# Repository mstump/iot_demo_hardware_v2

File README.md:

iot_demo_hardware_v2
====================

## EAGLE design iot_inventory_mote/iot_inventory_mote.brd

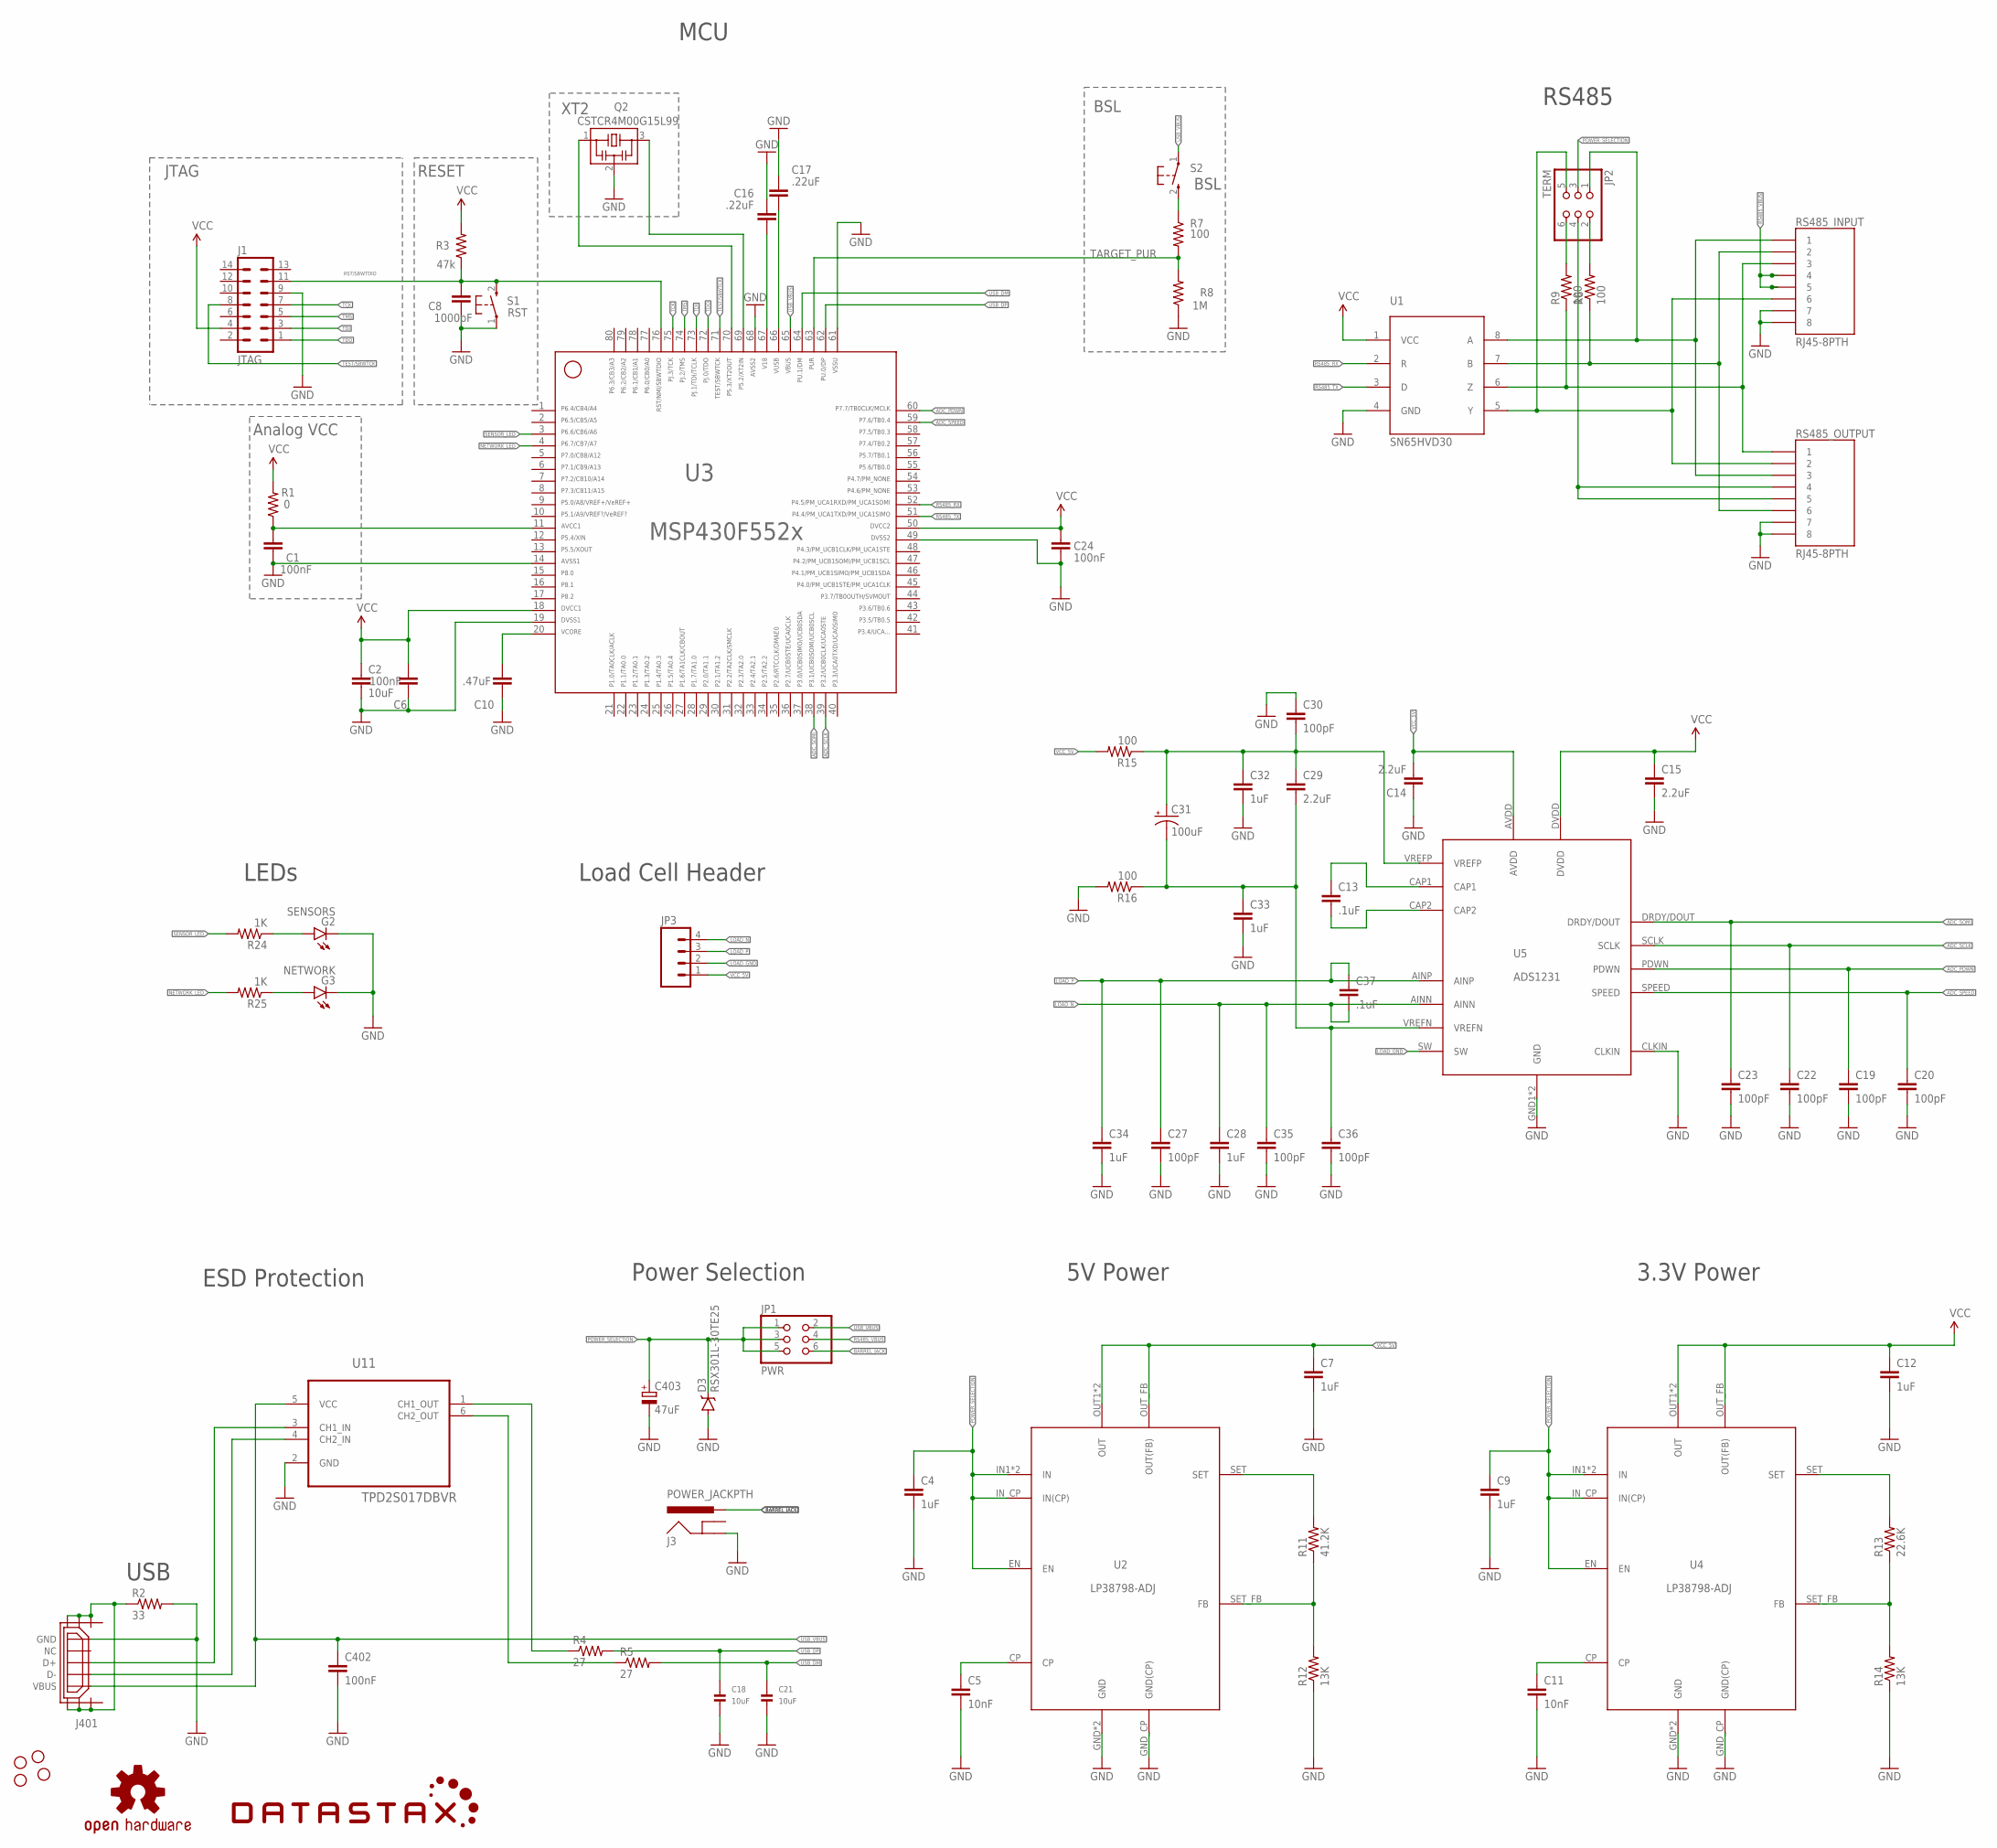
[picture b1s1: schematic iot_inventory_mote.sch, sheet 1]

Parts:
C1, C6, C24: 100nF; 0402-CAP
C2: 10uF; 0402-CAP
C4, C7, C9, C12: 1uF; 0402-CAP
C5, C11: 10nF; 0402-CAP
C8: 1000pF; 0402-CAP; MPN C1005X7R1H102K050BA
C10: .47uF; 0402-CAP
C13, C37: .1uF; 1210
C14, C15, C29: 2.2uF; 0402-CAP
C16, C17: .22uF; 0402-CAP
C18, C21: 10uF; 0603; MPN 06035A100FAT2A
C19, C20, C22, C23: 100pF; 0805
C27, C30, C35, C36: 100pF; 0603-CAP
C28, C32, C33, C34: 1uF; 0805
C31: 100uF; EIA7343
C402: 100nF; 0402-CAP; MPN 100NA100MEFC12.5X25
C403: 47uF; A/3216-18R
D3: RSX301L-30TE25; SMA-DIODE
G2: SENSORS; LED-0603
G3: NETWORK; LED-0603
J1: JTAG; ML14; MPN SBH11-PBPC-D07-ST-BK
J3: POWER_JACKPTH; POWER_JACK_PTH
J401: USB_MICRO_FLIPPED; HIROSE-ZX62R-B-5P; MPN ZX62R-B-5P
JP1: PWR; 2X03
JP2: TERM; 2X03
JP3: M04SCREW; SCREWTERMINAL-3.5MM-4
LOGO1: OSHW-LOGOL; OSHW-LOGO-L
Q2: CSTCR4M00G15L99; MURATA-FILTER_CSTCR
R1: 0; R0402
R2: 33; 0402-RES
R3: 47k; R0402; MPN ERJ-2RKF4702X
R4, R5: 27; 0402-RES
R6, R9, R15, R16: 100; 0402-RES
R7: 100; R0402
R8: 1M; R0402
R11: 41.2K; 0402-RES
R12, R14: 13K; 0402-RES
R13: 22.6K; 0402-RES
R24, R25: 1K; 0402-RES; MPN ERJ-2RKF1001X
RS485_INPUT, RS485_OUTPUT: RJ45-8PTH; RJ45-8; MPN 54602-908LF
S1: RST; PBTH; MPN EVQ-11L05R
S2: BSL; PBTH
STANDOFF1, STANDOFF2, STANDOFF3, STANDOFF4: STAND-OFF
U1: SN65HVD30; SOIC8; MPN SN65HVD3082EDR
U2, U4: LP38798-ADJ; WSON12; MPN LP38798SD-ADJ/NOPB
U3: MSP430F5529IPNR; PN80; MPN MSP430F5529IPNR
U5: ADS1231; MPN ADS1231ID
U11: TPD2S017DBVR; SOT95P280X145-6N
U$1: DATASTAX_LOGO

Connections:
ADC_PDWN: C19.1, U3.60, U5.PDWN
ADC_SCLK: C22.1, U3.39, U5.SCLK
ADC_SOMI: C23.1, U3.38, U5.DRDY/DOUT
ADC_SPEED: C20.1, U3.59, U5.SPEED
AVCC: C1.1, R1.1, U3.11
BARREL_JACK: J3.PWR, JP1.6
GND: C1.2, C2.2, C4.2, C5.2, C6.2, C7.2, C8.2, C9.2, C10.2, C11.2, C12.2, C14.1, C15.2, C16.2, C17.2, C18.2, C19.2, C20.2, C21.2, C22.2, C23.2, C24.2, C27.2, C28.2, C30.1, C32.2, C33.2, C34.2, C35.2, C36.2, C402.2, C403.-, D3.A, G2.C, G3.C, J1.9, J3.GND, J401.GND, Q2.2, R2.2, R8.1, R12.1, R14.1, R16.2, RS485_INPUT.7, RS485_INPUT.8, RS485_OUTPUT.7, RS485_OUTPUT.8, S1.1, U1.4 (GND), U2.GND, U2.GND_CP (GND(CP)), U2.GPAD (GND), U3.14, U3.19, U3.49, U3.61, U3.68, U4.GND, U4.GND_CP (GND(CP)), U4.GPAD (GND), U5.CLKIN, U5.GND1 (GND), U5.GND2 (GND), U11.2 (GND)
LOAD_GND: JP3.2, U5.SW
LOAD_N: C28.1, C35.1, C37.2, JP3.4, U5.AINN
LOAD_P: C27.1, C34.1, C37.1, JP3.3, U5.AINP
unnamed: JP2.2, R6.2
unnamed: R6.1, RS485_INPUT.2, RS485_OUTPUT.6, U1.7 (B)
unnamed: R9.1, RS485_INPUT.3, RS485_OUTPUT.1, U1.6 (Z)
unnamed: JP2.1, RS485_INPUT.1, RS485_OUTPUT.3, U1.8 (A)
unnamed: G3.A, R25.1
unnamed: JP2.6, R9.2
unnamed: JP2.5, RS485_INPUT.6, RS485_OUTPUT.2, U1.5 (Y)
unnamed: R13.2, U4.SET
unnamed: J401.D+, U11.3 (CH1_IN)
unnamed: R11.1, R12.2, U2.SET_FB (FB)
unnamed: R11.2, U2.SET
unnamed: C5.1, U2.CP
unnamed: J401.D-, U11.4 (CH2_IN)
unnamed: R13.1, R14.2, U4.SET_FB (FB)
unnamed: C11.1, U4.CP
unnamed: C13.1, U5.CAP1
unnamed: C13.2, U5.CAP2
unnamed: G2.A, R24.1
unnamed: J401.SHIELD1, J401.SHIELD2, J401.SHIELD3, J401.SHIELD4, J401.SHIELD5, J401.SHIELD6, R2.1
unnamed: C29.1, C30.2, C31.A (+), C32.1, R15.1, U5.VREFP
unnamed: R7.1, S2.2 (S)
unnamed: R5.1, U11.6 (CH2_OUT)
unnamed: R4.1, U11.1 (CH1_OUT)
unnamed: C29.2, C31.C (-), C33.1, C36.1, R16.1, U5.VREFN
unnamed: JP2.4, RS485_OUTPUT.4, RS485_OUTPUT.5
NETWORK_LED: R25.2, U3.4
P5.2/XT2IN: Q2.3, U3.69
P5.3/XT2OUT: Q2.1, U3.70
POWER_SELECTION: C4.1, C9.1, C403.+, D3.C, JP1.1, JP1.3, JP1.5, JP2.3, U2.EN, U2.IN1 (IN), U2.IN2 (IN), U2.IN_CP (IN(CP)), U4.EN, U4.IN1 (IN), U4.IN2 (IN), U4.IN_CP (IN(CP))
RS485_RX: U1.2 (R), U3.52
RS485_TX: U1.3 (D), U3.51
RS485_VBUS: JP1.4, RS485_INPUT.4, RS485_INPUT.5
RST/SBWTDIO: C8.1, J1.11, R3.1, S1.2 (S), U3.76
SENSOR_LED: R24.2, U3.3
TARGET_PUR: R7.2, R8.2, U3.63
TARGET_VUSB: C17.1, U3.66
TCK: J1.7, U3.75
TDI: J1.3, U3.73
TDO: J1.1, U3.72
TEST/SBWTCK: J1.8, U3.71
TMS: J1.5, U3.74
USB_DM: C21.1, R5.2, U3.64
USB_DP: C18.1, R4.2, U3.62
USB_VBUS: C402.1, J401.VBUS, JP1.2, S2.1, U3.65, U11.5 (VCC)
V18: C16.1, U3.67
VCC: C2.1, C6.1, C12.1, C15.1, C24.1, J1.4, R1.2, R3.2, U1.1 (VCC), U3.18, U3.50, U4.OUT1 (OUT), U4.OUT2 (OUT), U4.OUT_FB (OUT(FB)), U5.DVDD
VCC_5V: C7.1, C14.2, JP3.1, R15.2, U2.OUT1 (OUT), U2.OUT2 (OUT), U2.OUT_FB (OUT(FB)), U5.AVDD
VCORE: C10.1, U3.20

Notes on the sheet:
USB
ESD Protection
RESET
XT2
BSL
Analog VCC
MCU
5V Power
JTAG
LEDs
RS485
3.3V Power
Power Selection
Load Cell Header

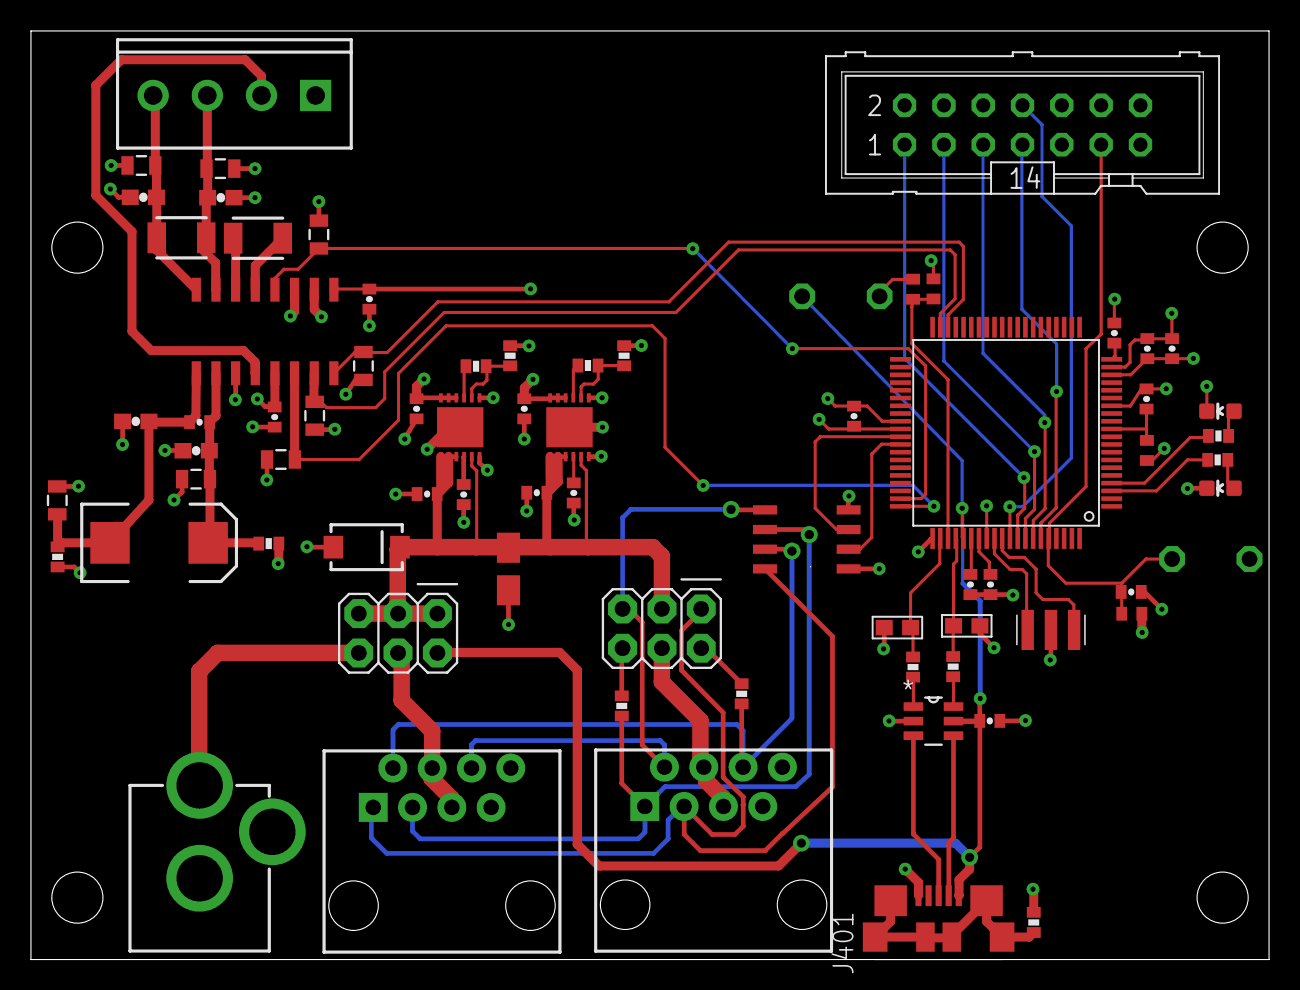
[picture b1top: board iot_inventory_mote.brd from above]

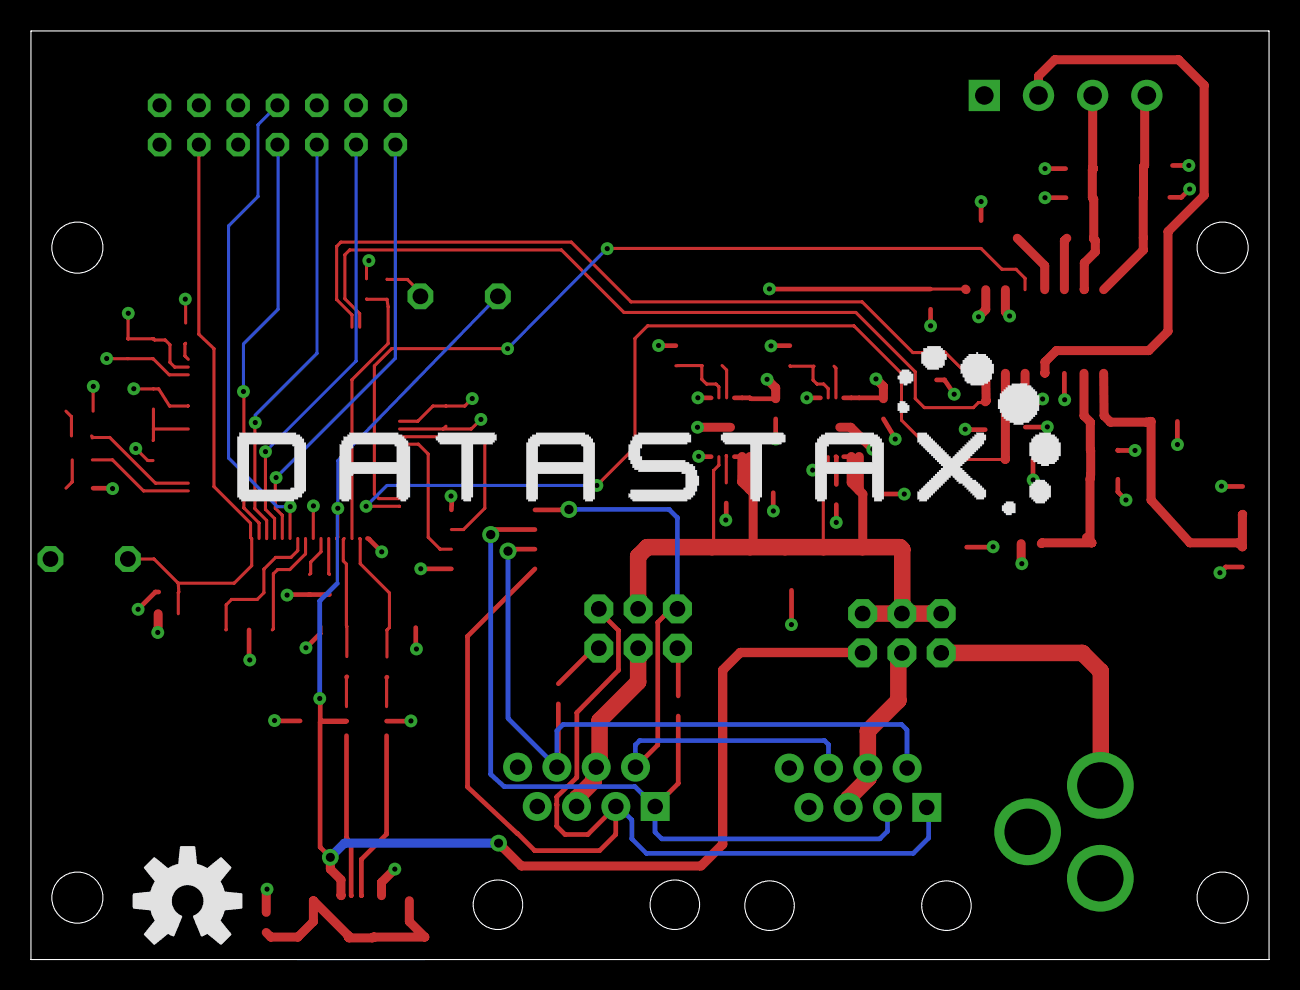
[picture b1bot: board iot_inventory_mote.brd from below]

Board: 4 copper layers, 80.0 x 60.0 mm, 79 parts (2 on the bottom side), 58 nets.

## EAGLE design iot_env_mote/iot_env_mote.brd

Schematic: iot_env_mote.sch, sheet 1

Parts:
C1, C2, C6, C24: 100n; C0402
C3: 10u; A/3216-18R
C4, C12, C13: 10uF; 0805; MPN 06035A100FAT2A
C5: 2.2uF; 0805; MPN 06035A100FAT2A
C7, C11, C19, C31: 0.1uF; 0603; MPN 0603YC104JAT2A
C8: 1nF; C0402
C9, C18, C21: 10uF; 0603; MPN 06035A100FAT2A
C10: 470n; C0402
C16, C17: 220n; C0402
C22: 10uF; A/3216-18R
C23, C25: 1uF; 0603; MPN 06035A100FAT2A
C26, C27, C30, C33, C34, C38, C40, C42, C45, C48: 47nF; 0402-CAP; MPN 0603YC104JAT2A
C28, C32, C174: 15pF; 0402-CAP; MPN 0603YC104JAT2A
C29: 220nF; 0402-CAP; MPN 0603YC104JAT2A
C171: 10pF; 0402-CAP; MPN 0603YC104JAT2A
C172: 100pF; 0402-CAP; MPN 0603YC104JAT2A
C173: 33pF; 0402-CAP; MPN 0603YC104JAT2A
C175: 3pF; 0402-CAP; MPN 0603YC104JAT2A
C176: 1pF; 0402-CAP; MPN 0603YC104JAT2A
C181: 2.2pF; 0402-CAP; MPN 0603YC104JAT2A
C191, C201: 3.3pF; 0402-CAP; MPN 0603YC104JAT2A
C211: 10nF; 0402-CAP; MPN 0603YC104JAT2A
C221: 46nF; 0402-CAP; MPN 0603YC104JAT2A
C231: 1.5nF; 0402-CAP; MPN 0603YC104JAT2A
C402: 100nF; C0402
C403: 47uF; A/3216-18R
CHARGE: LED0603; LED-0603
CN1: USB; USB-MINIB
D8, D10: 0.01; R0402
D9: 1M; R0402
G1: SD/FLASH; LED-0603
G2: SENSORS; LED-0603
G3: NETWORK; LED-0603
J1: JTAG; ML14
J2: IO BREAKOUT; 2X10
J3: BATTERY; JST-PH-2-SMT-RA
JP2: MOTION; JST-3-PTH-VERT
L10: 4.7uH; SDR0403
L171: 10nH; C0402
L172: 7.5nH; C0402
L173: 18nH; C0402
L174, L192, L193, L201: 12nH; C0402
L191: 15nH; C0402
LOGO1: OSHW-LOGOL; OSHW-LOGO-L
POWER: LED0603; LED-0603
Q1: 32.768kHz; MS3V-T1R
Q2: CSTCR4M00G15L99; MURATA-FILTER_CSTCR
Q3: 40MHz; NX3225
Q4, Q5: BSS84; SOT23
R1: 0R; R0402
R2: 33k; 0402-RES
R3: 47k; R0402
R4, R5: 27; 0402-RES
R6, R27: 1K; R0402
R7: 100R; R0402
R8: 1M; R0402
R9, R18, R19, R20, R21, R23: 10K; R0402; MPN ERJ-P03F1002V
R10, R24, R25: 1K; 0402-RES
R12: 56k; 0402-RES
R16: 332K; R0402
R17: 649K; R0402
R26: 1.87K; R0402
R171: 10; 0402-RES
R181: 0; 0402-RES
S1: RST; PBTH
S2: BSL; PBTH
S3: DPDT; AYZ0202
SMA: SMA_EDGE; SMA-EDGE
U1: LTC3553-2; QFN-20-0.4MM
U2: MPL3115A2LGA8; LGA8; MPN MPL3115A2
U3: MSP430F5529IPNR; PN80
U4: HTU21DSMD; HTU21D; MPN HTU21D
U5: USD-SOCKETNEW; MICRO-SD-SOCKET-PP
U6: BQ27411; VSON40P400X400X12
U7: TSL2561FN; FN-6; MPN TSL2561T
U8: CC1200; RHB32
U11: TPD2S017DBVR; SOT95P280X145-6N
U$1: DATASTAX_LOGO

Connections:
AVCC: C1.1, R1.1, U3.11
BQ27411_BAT: C25.2, D8.2, J3.1 (2), U6.BAT, U6.SRP
FLASH_CD: U3.30, U5.CD1 (SHIELD)
FLASH_CSN: U3.29, U5.2 (CS)
FLASH_ENABLE: Q5.1 (G), U3.17
GND: C1.2, C2.1, C3.-, C4.2, C5.2, C6.1, C7.2, C8.2, C9.2, C10.1, C11.2, C13.2, C16.2, C17.2, C18.2, C19.2, C21.2, C22.-, C23.2, C24.2, C25.1, C26.2, C27.2, C28.2, C29.2, C30.2, C31.2, C32.2, C33.2, C34.2, C38.2, C40.2, C42.2, C45.2, C48.2, C171.2, C172.2, C175.2, C201.2, C211.2, C402.2, C403.-, D9.2, D10.2, J1.9, J2.2, J3.2 (1), JP2.1, L192.2, Q1.P3 (GND), Q2.2, Q3.2 (G2), Q3.4 (G1), R2.2, R8.1, R10.1, R12.2, R17.2, R24.1, R25.1, R26.1, R27.1, S1.1, SMA.GND@0 (GND), SMA.GND@1 (GND), SMA.GND@2 (GND), SMA.GND@3 (GND), U1.2 (SEQ), U1.5 (LDO_ON), U1.6 (STBY), U1.15 (NTC), U1.19 (SUSP), U1.21 (GND_PAD), U2.3 (GND), U3.14, U3.19, U3.49, U3.61, U3.68, U4.7 (GND), U4.GND, U5.6 (GND), U5.GND1 (SHIELD), U5.GND3 (SHIELD), U6.GND (TPAD), U6.VSS, U7.2 (ADDR), U7.3 (GND), U8.TP (33), U11.2 (GND)
I2C_SCL: J2.4, R18.1, R21.1, U2.8 (SCL), U3.47, U4.SCK, U6.SCL, U7.4 (SCL)
I2C_SDA: J2.6, R19.1, R20.1, U2.7 (SDA), U3.46, U4.DATA, U6.SDA, U7.6 (SDA)
IO_LED: G1.A, U3.26
IO_SCK: U3.36, U5.5 (SCK)
IO_SIMO: U3.40, U5.3 (DI)
IO_SOMI: U3.41, U5.7 (DO)
JTAG_SENSE: J1.4, S3.5
JTAG_VCC: J1.2, S3.3
LDO: U1.10 (LDO)
LDO_FB: U1.9 (LDO_FB)
LIGHT_INT: R9.1, U3.58, U7.5 (INT)
MOTION_ENABLE: Q4.1 (G), U3.59
MOTION_INT: JP2.2, U3.60
unnamed: C11.1, U2.2 (CAP)
unnamed: JP2.3, Q4.2 (S)
unnamed: C174.1, L171.1, U8.17
unnamed: Q5.2 (S), U5.4 (VCC), U5.8 (RSV)
unnamed: C231.2, U8.23
unnamed: CN1.D+, U11.3 (CH1_IN)
unnamed: C23.1, U6.VDD
unnamed: D10.1, U6.TEST
unnamed: C231.1, U8.24
unnamed: CN1.D-, U11.4 (CH2_IN)
unnamed: D9.1, U6.PROG
unnamed: C211.1, U8.21
unnamed: C174.2, C176.1, L172.1
unnamed: C29.1, U8.6
unnamed: C176.2, C181.2, L172.2, L173.1
unnamed: L174.2, R181.1
unnamed: C181.1, L193.2, U8.18
unnamed: C221.2, U8.22
unnamed: R181.2, SMA.SIG (SIGNAL)
unnamed: C175.1, L173.2, L174.1
unnamed: CN1.GND, R2.1
unnamed: C173.2, L171.2, R171.1
unnamed: C28.1, Q3.1 (X1), U8.30
unnamed: C191.1, L191.1, L192.1, U8.19
unnamed: C201.1, L191.2, L201.1, U8.20
unnamed: C32.1, Q3.3 (X2), U8.31
unnamed: G1.C, R10.2
unnamed: C191.2, L193.1, L201.2
unnamed: L10.2, U1.13 (SW)
unnamed: R12.1, U8.14
unnamed: R7.1, S2.2 (S)
unnamed: G2.C, R24.2
unnamed: G3.C, R25.2
unnamed: R5.1, U11.6 (CH2_OUT)
unnamed: R4.1, U11.1 (CH1_OUT)
unnamed: CHARGE.C, R6.1
unnamed: C4.1, C5.1, CHARGE.A, POWER.A, U1.12 (BVIN), U1.18 (VOUT)
unnamed: R6.2, U1.14 (CHRG)
unnamed: POWER.C, R27.2
unnamed: C12.2, R16.1, R17.1, U1.8 (BUCK_FB)
unnamed: R26.2, U1.16 (PROG)
P1.0: J2.20, U3.21
P1.1: J2.17, U3.22
P1.2: J2.18, U3.23
P1.3: J2.15, U3.24
P1.4: J2.16, U3.25
P2.2: J2.13, U3.31
P2.3: J2.14, U3.32
P2.4: J2.11, U3.33
P2.5: J2.12, U3.34
P2.6: J2.9, U3.35
P5.2/XT2IN: Q2.3, U3.69
P5.3/XT2OUT: Q2.1, U3.70
P5.4/XIN: Q1.P2 (2), U3.12
P5.5/XOUT: Q1.P1 (1), U3.13
PRESSURE_INT: R23.1, U2.6 (INT1), U3.43
REGULATOR_BUCK_ON: U1.7 (BUCK_ON), U3.2
REGULATOR_HPWR: U1.1 (HPWR), U3.1
REGULATOR_VCC: C12.1, C13.1, L10.1, R16.2, S3.1, S3.4
RF_CLK: U3.39, U8.8
RF_CSN: U3.53, U8.11
RF_GPIO0: U3.54, U8.10
RF_GPIO2: U3.55, U8.4
RF_GPIO3: U3.56, U8.3
RF_LED: G3.A, U3.28
RF_RESET: U3.57, U8.2
RF_SIMO: U3.37, U8.7
RF_SOMI: U3.38, U8.9
RST/SBWTDIO: C8.1, J1.11, R3.1, S1.2 (S), U3.76
SENSOR_LED: G2.A, U3.27
TARGET_PUR: R7.2, R8.2, U3.63
TARGET_VUSB: C17.1, U3.66
TCK: J1.7, U3.75
TDI: J1.3, U3.73
TDO: J1.1, U3.72
TEST/SBWTCK: J1.8, U3.71
TMS: J1.5, U3.74
UCA1_CLK: J2.10, U3.45
UCA1_RXD: J2.3, U3.52
UCA1_STE: J2.8, U3.48
UCA1_TXD: J2.5, U3.51
USB_DM: C21.1, R5.2, U3.64
USB_DP: C18.1, R4.2, U3.62
USB_VBUS: C402.1, C403.+, CN1.VBUS, J2.19, S2.1, U1.20 (VBUS), U3.65, U11.5 (VCC)
V18: C16.1, U3.67
VBAT+: D8.1, U1.17 (BAT), U6.SRN
VCC: C2.2, C3.+, C6.2, C7.1, C9.1, C19.1, C22.+, C24.1, C26.1, C27.1, C30.1, C31.1, C33.1, C34.1, C38.1, C40.1, C42.1, C45.1, C48.1, C171.1, C172.1, C173.1, C221.1, J2.1, Q4.3 (D), Q5.3 (D), R1.2, R3.2, R9.2, R18.2, R19.2, R20.2, R21.2, R23.2, R171.2, S3.2, U2.1 (VDD), U2.4 (VDDIO), U3.18, U3.50, U4.VDD, U7.1 (VDD), U8.1, U8.5, U8.12, U8.13, U8.15, U8.25, U8.26, U8.27, U8.28, U8.29
VCORE: C10.2, U3.20
VINLDO: U1.11 (VINLDO)

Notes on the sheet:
Humidity
Pressure
Sensors
I2C address is 0x40 I2C write is 0x80 I2C read is 0x81
I2C address is 0x60 I2C write is 0xC0 I2C read is 0xC1
Light
I2C address is 0x41
Battery Charger / Regulator
Battery Gauge
USB
ESD Protection
Radio
RESET
LFXTCLK
XT2
BSL
Analog VCC
MCU
Power Selection
JTAG
IO Breakout
MicroSD Flash
LEDs

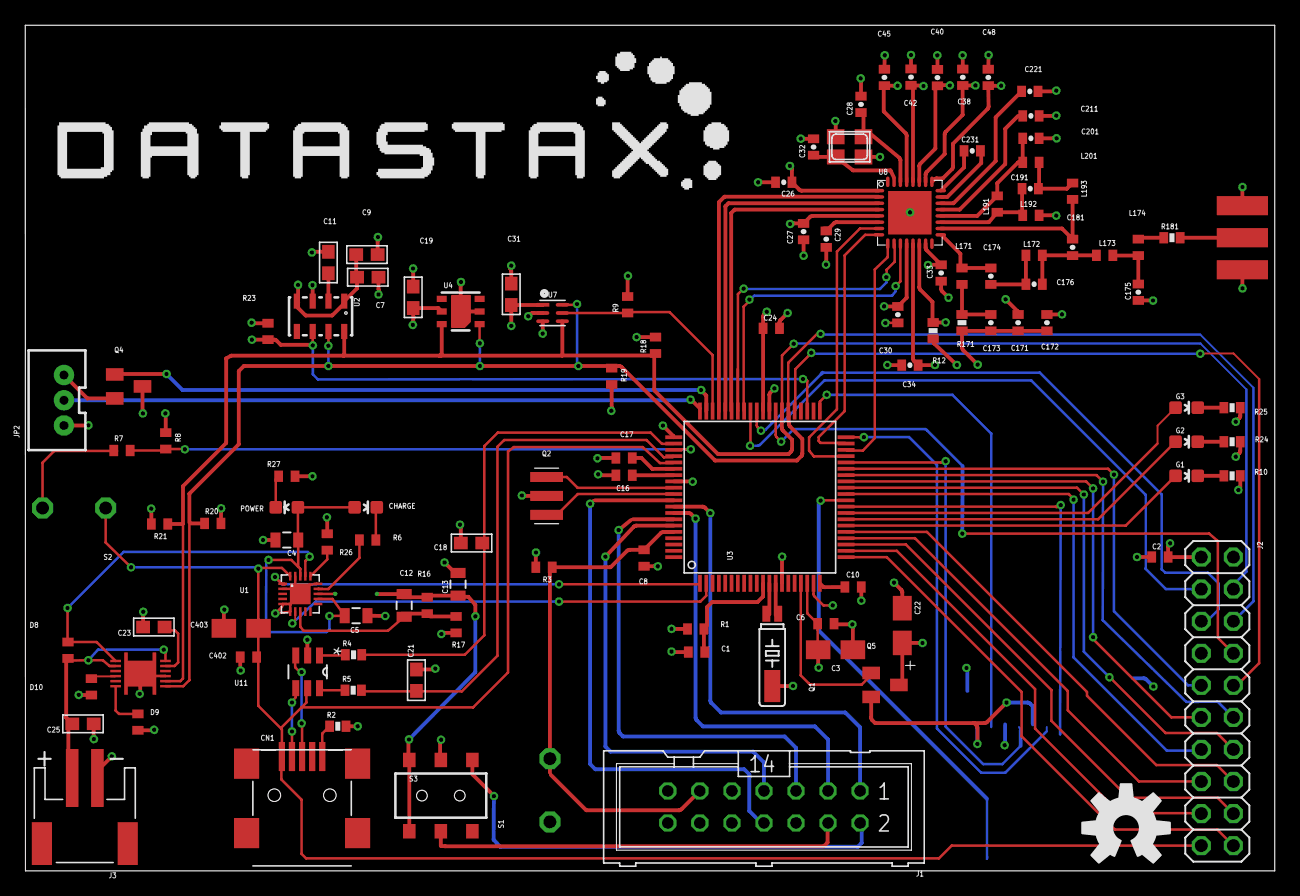
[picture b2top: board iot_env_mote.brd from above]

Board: 4 copper layers, 99.0 x 67.0 mm, 116 parts (1 on the bottom side), 105 nets.

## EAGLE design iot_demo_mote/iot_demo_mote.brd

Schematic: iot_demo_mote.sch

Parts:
C1, C2, C5, C7: 0.1uF; 0603; MPN 0603YC104JAT2A
C3, C14, C42, C43: 10uF; 0603; MPN 06035A100FAT2A
C4, C12: 1uF; 0603; MPN 06035A100FAT2A
C6: 47uF; 0402-CAP; MPN 06035A100FAT2A
C8: 10uF / 10V; 0603; MPN 06035A100FAT2A
C9, C10: 1uF / 10V; 0603; MPN 06035A100FAT2A
C11, C15: 150 pF; 0603; MPN 06035A100FAT2A
C13: .033uF; 0603; MPN 06035A100FAT2A
C16: 1.5nF; 0402-CAP; MPN 0603YC104JAT2A
C17, C23: 10nF; 0402-CAP; MPN 0603YC104JAT2A
C18, C19, C20, C21, C22, C26, C27, C29, C30, C31: 47nF; 0402-CAP; MPN 0603YC104JAT2A
C24, C39, C40: 15pF; 0402-CAP; MPN 0603YC104JAT2A
C25: 46nF; 0402-CAP; MPN 0603YC104JAT2A
C28: 220nF; 0402-CAP; MPN 0603YC104JAT2A
C32: 2.2pF; 0402-CAP; MPN 0603YC104JAT2A
C33, C34, C35, C36: 3pF; 0402-CAP; MPN 0603YC104JAT2A
C37, C38: 3.3pF; 0402-CAP; MPN 0603YC104JAT2A
C41: 470pF; 0402-CAP; MPN 06035A100FAT2A
C44, C50, C53, C57: 100n; C0402
C45: 10uF; 0402-CAP; MPN 06035A100FAT2A
C46, C47: 220n; C0402
C48: 1n; C0402
C49: 470n; C0402
C51, C52: 12p; C0402
C54: 10u; A/3216-18R
C55: 10uF; A/3216-18R
C59: 4u7; C0603
C60: 0.1u; C0603
CHARGE: ORANGE; LED-0603
CN4: USB; USB-MINIB
D1, D5, D8: 1M ohm; R0402
D3, D4: 0.01 ohm; R0402
D6, D7: 300 ohm; R0402
D9, D10: 100 ohm; R0402
D11: SCHOTTKY; MINIMELF
G1: SD ACTIVITY; LED-0603
J1, J5: IO BREAKOUT; 2X10
J2: JTAG; ML14
J3: BATTERY; JST-PH-2-SMT-RA
J$1: SMA_EDGE; SMA-EDGE
JP1: MOTION; JST-3-PTH-VERT
JP2: M01OFFSET; 1X01_OFFSET
L1: 7.5nH; C0402
L2: 2.2uH; SDR0403
L3: 18nH; C0402
L4, L6, L7, L9: 12nH; C0402
L5: 10nH; C0402
L8: 15nH; C0402
POWER: RED; LED-0603
Q1: 40MHz; NX3225
Q2: 32.768kHz; MS3V-T1R
Q4: CSTCR4M00G15L99; MURATA-FILTER_CSTCR
R1: 0; 0402-RES
R2, R3: 1K; R0402
R4: 10K; R0402; MPN ERJ-P03F1002V
R5: 10ohm; 0402-RES
R6: 56k; 0402-RES
R7, R8: 27ohm; 0402-RES
R9: 33k; 0402-RES
R10: 1K; 0402-RES
R14: 100R; R0402
R15: 1k4; R0402
R16: 1M; R0402
R27: 47k; R0402
R28: 0R; R0402
S2: DPDT; AYZ0202
S3: RST; PBTH
S5: BSL; PBTH
U1: MSP430F5529IPNR; PN80
U2: CC1200; RHB32
U3: HTU21DSMD; HTU21D; MPN HTU21D
U4: MPL3115A2LGA8; LGA8; MPN MPL3115A2
U5: TSL2561FN; FN-6; MPN TSL2561T
U6: BQ27411; VSON40P400X400X12
U7: TPD2E001IDRLRQ1; SOT50P160X60-5N
U8: MIC52053.3V; SOT23-5
U9: USD-SOCKETNEW; MICRO-SD-SOCKET-PP
U$3: BQ24262; QFN50P400X400X80-25N

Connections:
AVCC: C53.1, R28.1, U1.11
BQ27411_BAT: C9.2, D3.1, J3.1 (2), U6.P$6 (BAT), U6.P$8 (SRP)
CHARGE_INT: U1.53, U$3.10 (INT)
DO_SOMETHING_WITH_ME: U$3.5 (TS)
FLASH_CD: U1.55, U9.CD1 (SHIELD)
FLASH_CSN: R10.1, U1.56, U9.2 (CS)
GND: C1.2, C2.2, C3.2, C4.2, C5.2, C6.2, C7.2, C8.2, C9.1, C10.2, C11.2, C12.2, C14.2, C15.2, C17.2, C18.2, C19.2, C20.2, C21.2, C22.2, C26.2, C27.2, C28.2, C29.2, C30.2, C31.2, C33.2, C35.2, C36.2, C38.2, C39.2, C40.2, C41.2, C42.2, C43.2, C44.2, C46.2, C47.2, C48.2, C49.1, C50.1, C51.1, C52.1, C53.2, C54.-, C55.-, C57.1, C59.2, C60.2, D1.1, D4.2, D5.2, D8.1, J2.9, J3.2 (1), J5.2, J$1.GND@0 (GND), J$1.GND@1 (GND), J$1.GND@2 (GND), J$1.GND@3 (GND), JP1.1, L6.2, Q1.2 (G2), Q1.4 (G1), Q2.P3 (GND), Q4.2, R3.2, R6.2, R9.2, R16.1, S3.1, U1.14, U1.19, U1.49, U1.61, U1.68, U3.7 (GND), U3.GND, U4.3 (GND), U5.2 (ADDR), U5.3 (GND), U6.P$3 (VSS), U6.P$13 (TPAD), U7.4 (GND), U8.2 (GND), U9.6 (GND), U9.GND1 (SHIELD), U9.GND3 (SHIELD), U$3.4 (CD), U$3.12 (AGND1), U$3.20 (AGND2), U$3.21 (PGND1), U$3.22 (PGND2), U$3.25 (TPAD)
I2C_SCL: D10.2, U1.47, U3.SCK, U4.8 (SCL), U5.4 (SCL)
I2C_SDA: D9.2, U1.46, U3.DATA, U4.7 (SDA), U5.6 (SDA)
IO_CLK: G1.A, U1.36, U9.5 (SCK)
IO_SIMO: U1.40, U9.3 (DI)
IO_SOMI: U1.41, U9.7 (DO)
JTAG_SENSE: J2.4, S2.5
JTAG_VCC: J2.2, S2.3
LIGHT_INT: R4.1, U1.58, U5.5 (INT)
MOTION_INT: JP1.2, U1.60
unnamed: C5.1, U4.2 (CAP)
unnamed: C4.1, CHARGE.A, POWER.A, U$3.3 (DRV)
unnamed: C24.1, L5.1, U2.17
unnamed: CHARGE.C, R2.1
unnamed: R2.2, U$3.13 (STAT)
unnamed: C12.1, U$3.1 (PMID)
unnamed: POWER.C, R3.1
unnamed: C16.2, U2.23
unnamed: C15.1, D7.2, D8.2, D10.1
unnamed: C10.1, U6.P$5 (VDD)
unnamed: D4.1, U6.P$10 (TEST)
unnamed: C16.1, U2.24
unnamed: C11.1, D1.2, D6.2, D9.1
unnamed: D5.1, JP2.1, U6.P$12 (PROG)
unnamed: C17.1, U2.21
unnamed: C23.1, C24.2, L1.1
unnamed: C28.1, U2.6
unnamed: C13.1, L2.2, U$3.23 (SW1), U$3.24 (SW2)
unnamed: C23.2, C32.2, L1.2, L3.1
unnamed: C13.2, U$3.2 (BOOT)
unnamed: L4.2, R1.1
unnamed: C32.1, L9.2, U2.18
unnamed: C25.2, U2.22
unnamed: J$1.SIG (SIGNAL), R1.2
unnamed: C33.1, L3.2, L4.1
unnamed: CN4.GND, R9.1
unnamed: C34.2, L5.2, R5.1
unnamed: C40.1, Q1.1 (X1), U2.30
unnamed: C37.1, L6.1, L8.1, U2.19
unnamed: C38.1, L7.1, L8.2, U2.20
unnamed: C39.1, Q1.3 (X2), U2.31
unnamed: C45.2, U8.5 (OUT)
unnamed: C37.2, L7.2, L9.1
unnamed: CN4.VBUS, D11.A, U7.1 (VCC)
unnamed: R6.1, U2.14
unnamed: R14.1, S5.2 (S)
unnamed: C41.1, U8.4 (BP)
unnamed: G1.C, R10.2
P1.0: J5.15, U1.21
P1.1: J5.13, U1.22
P1.2: J5.11, U1.23
P1.3: J5.9, U1.24
P1.4: J5.7, U1.25
P1.5: J5.5, U1.26
P1.6: J1.9, J5.3, U1.27
P1.7: J5.1, U1.28
P2.0: J1.13, U1.29
P2.1: J1.15, U1.30
P2.2: J5.6, U1.31
P2.3: J5.18, U1.32
P2.4: J1.17, U1.33
P2.5: J1.19, U1.34
P2.6: J1.16, J5.16, U1.35
P3.5: J1.20, U1.42
P3.6: J1.18, U1.43
P3.7: J5.17, U1.44
P5.0: J1.5, U1.9
P5.1: J1.7, U1.10
P5.2/XT2IN: Q4.3, U1.69
P5.3/XT2OUT: Q4.1, U1.70
P5.4/XIN: C52.2, Q2.P2 (2), U1.12
P5.5/XOUT: C51.2, Q2.P1 (1), U1.13
P6.0: J1.6, U1.77
P6.1: J1.8, U1.78
P6.2: J1.10, U1.79
P6.3: J1.12, U1.80
P6.4: J1.14, U1.1
P6.5: J1.3, U1.2
P6.6: J1.11, U1.3
P6.7: J1.4, U1.4
P8.1: J5.14, U1.16
P8.2: J5.19, U1.17
PRESSURE_INT: U1.59, U4.6 (INT1)
PWR_SCL: D7.1, U6.P$2 (SCL), U$3.16 (SCL)
PWR_SDA: D6.1, U6.P$1 (SDA), U$3.17 (SDA)
REGULATOR_VCC: C45.1, S2.1, S2.4
RF_CLK: U1.39, U2.8
RF_CSN: U1.5, U2.11
RF_GPIO0: U1.7, U2.10
RF_GPIO2: U1.8, U2.4
RF_GPIO3: U1.57, U2.3
RF_RESET: U1.6, U2.2
RF_SIMO: U1.37, U2.7
RF_SOMI: U1.38, U2.9
RST/SBWTDIO: C48.1, J2.11, J5.10, R27.1, S3.2 (S), U1.76
TARGET_PUR: R14.2, R15.1, R16.2, U1.63
TARGET_VUSB: C47.1, U1.66
TCK: J2.7, U1.75
TDI: J2.3, U1.73
TDO: J2.1, U1.72
TEST/SBWTCK: J2.8, U1.71
TMS: J2.5, U1.74
UCA1_CLK: J5.4, U1.45
UCA1_RXD: J5.20, U1.52
UCA1_STE: J5.12, U1.48
UCA1_TXD: J5.8, U1.51
USB_D+: CN4.D+, R7.1, U7.3 (IO1)
USB_D-: CN4.D-, R8.1, U7.5 (IO2)
USB_DM: C42.1, R8.2, U1.64
USB_DP: C43.1, R7.2, R15.2, U1.62
USB_VBUS: C8.1, C59.1, C60.1, D11.C, J1.2, S5.1, U1.65, U$3.14 (PSEL), U$3.18 (IN1), U$3.19 (IN2)
V18: C46.1, U1.67
VBAT+: D3.2, U6.P$7 (SRN), U$3.8 (BAT1), U$3.9 (BAT2)
VCC: C1.1, C2.1, C3.1, C7.1, C18.1, C19.1, C20.1, C21.1, C22.1, C25.1, C26.1, C27.1, C29.1, C30.1, C31.1, C34.1, C35.1, C36.1, C44.1, C50.2, C54.+, C55.+, C57.2, J1.1, JP1.3, R4.2, R5.2, R27.2, R28.2, S2.2, U1.18, U1.50, U2.1, U2.5, U2.12, U2.13, U2.15, U2.25, U2.26, U2.27, U2.28, U2.29, U2.TP (33), U3.VDD, U4.1 (VDD), U4.4 (VDDIO), U5.1 (VDD), U9.4 (VCC)
VCORE: C49.2, U1.20
VOUT_CHRG: C6.1, C14.1, L2.1, U8.1 (IN), U8.3 (EN), U$3.6 (SYS1), U$3.7 (SYS2)

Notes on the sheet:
Humidity
Pressure
Sensors
I2C address is 0x40 I2C write is 0x80 I2C read is 0x81
I2C address is 0x60 I2C write is 0xC0 I2C read is 0xC1
Light
I2C address is 0x41
Battery Charger
Battery Gauge
USB
ESD Protection
Regulator
Radio
RESET
LFXTCLK
XT2
BSL
Speed
Analog VCC
MCU
Power Selection
JTAG
IO Breakout
MicroSD Flash

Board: 2 copper layers, 119 parts (0 on the bottom side), 121 nets, no tracks yet.

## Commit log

2014-07-25 everything except the MCU
2014-07-28 flash, jtag, and spi
2014-07-28 schematic is functionally done
2014-07-28 added datastax and open hardware logos
2014-07-28 rename to make room for the scale mote
2014-07-31 semi-routed
2014-08-03 mostly routed
2014-08-04 routed
2014-08-05 final env board layout
2014-08-17 final inventory board
2014-08-19 increased annular ring, order placed

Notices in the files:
parts and their libraries:
SparkFun-Sensors: Licensing: Creative Commons ShareAlike 4.0 International - https://creativecommons.org/licenses/by-sa/4.0
